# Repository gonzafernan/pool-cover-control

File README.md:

# Pool Cover Control Board

Electronic control board for an automatic residential pool cover. Drives a 24V DC brushed motor in both directions using a relay H-bridge, with inputs from a key switch and mechanical limit switches.

## Overview

The board replaces a failed original controller. It is designed for direct drop-in installation into the existing enclosure, preserving all external wiring and mechanical components.

## Hardware

- **MCU:** STM32G031K8T6 (ARM Cortex-M0+, 64MHz, no external crystal)
- **Motor control:** 4x SLA-24VDC-SL-C SPDT relays in H-bridge configuration, driven by ULN2003A
- **Power input:** 24V, 10A fused, from external 25A/600W PSU in the same enclosure
- **Logic supply:** 3.3V via LMR14206XMKE/NOPB synchronous buck converter
- **Inputs:** 3-position maintained key switch, two NC limit switches, isolated via PC817 optocouplers
- **Protection:** Reverse polarity (P-FET), motor TVS, relay hardware interlock, firmware watchdog
- **Manufacturer:** JLCPCB

## Firmware

- Toolchain: STM32CubeMX + Makefile + GCC
- State machine: IDLE / OPENING / CLOSING / FAULT
- Motor timeout: 60 seconds
- Internal IWDG watchdog enabled

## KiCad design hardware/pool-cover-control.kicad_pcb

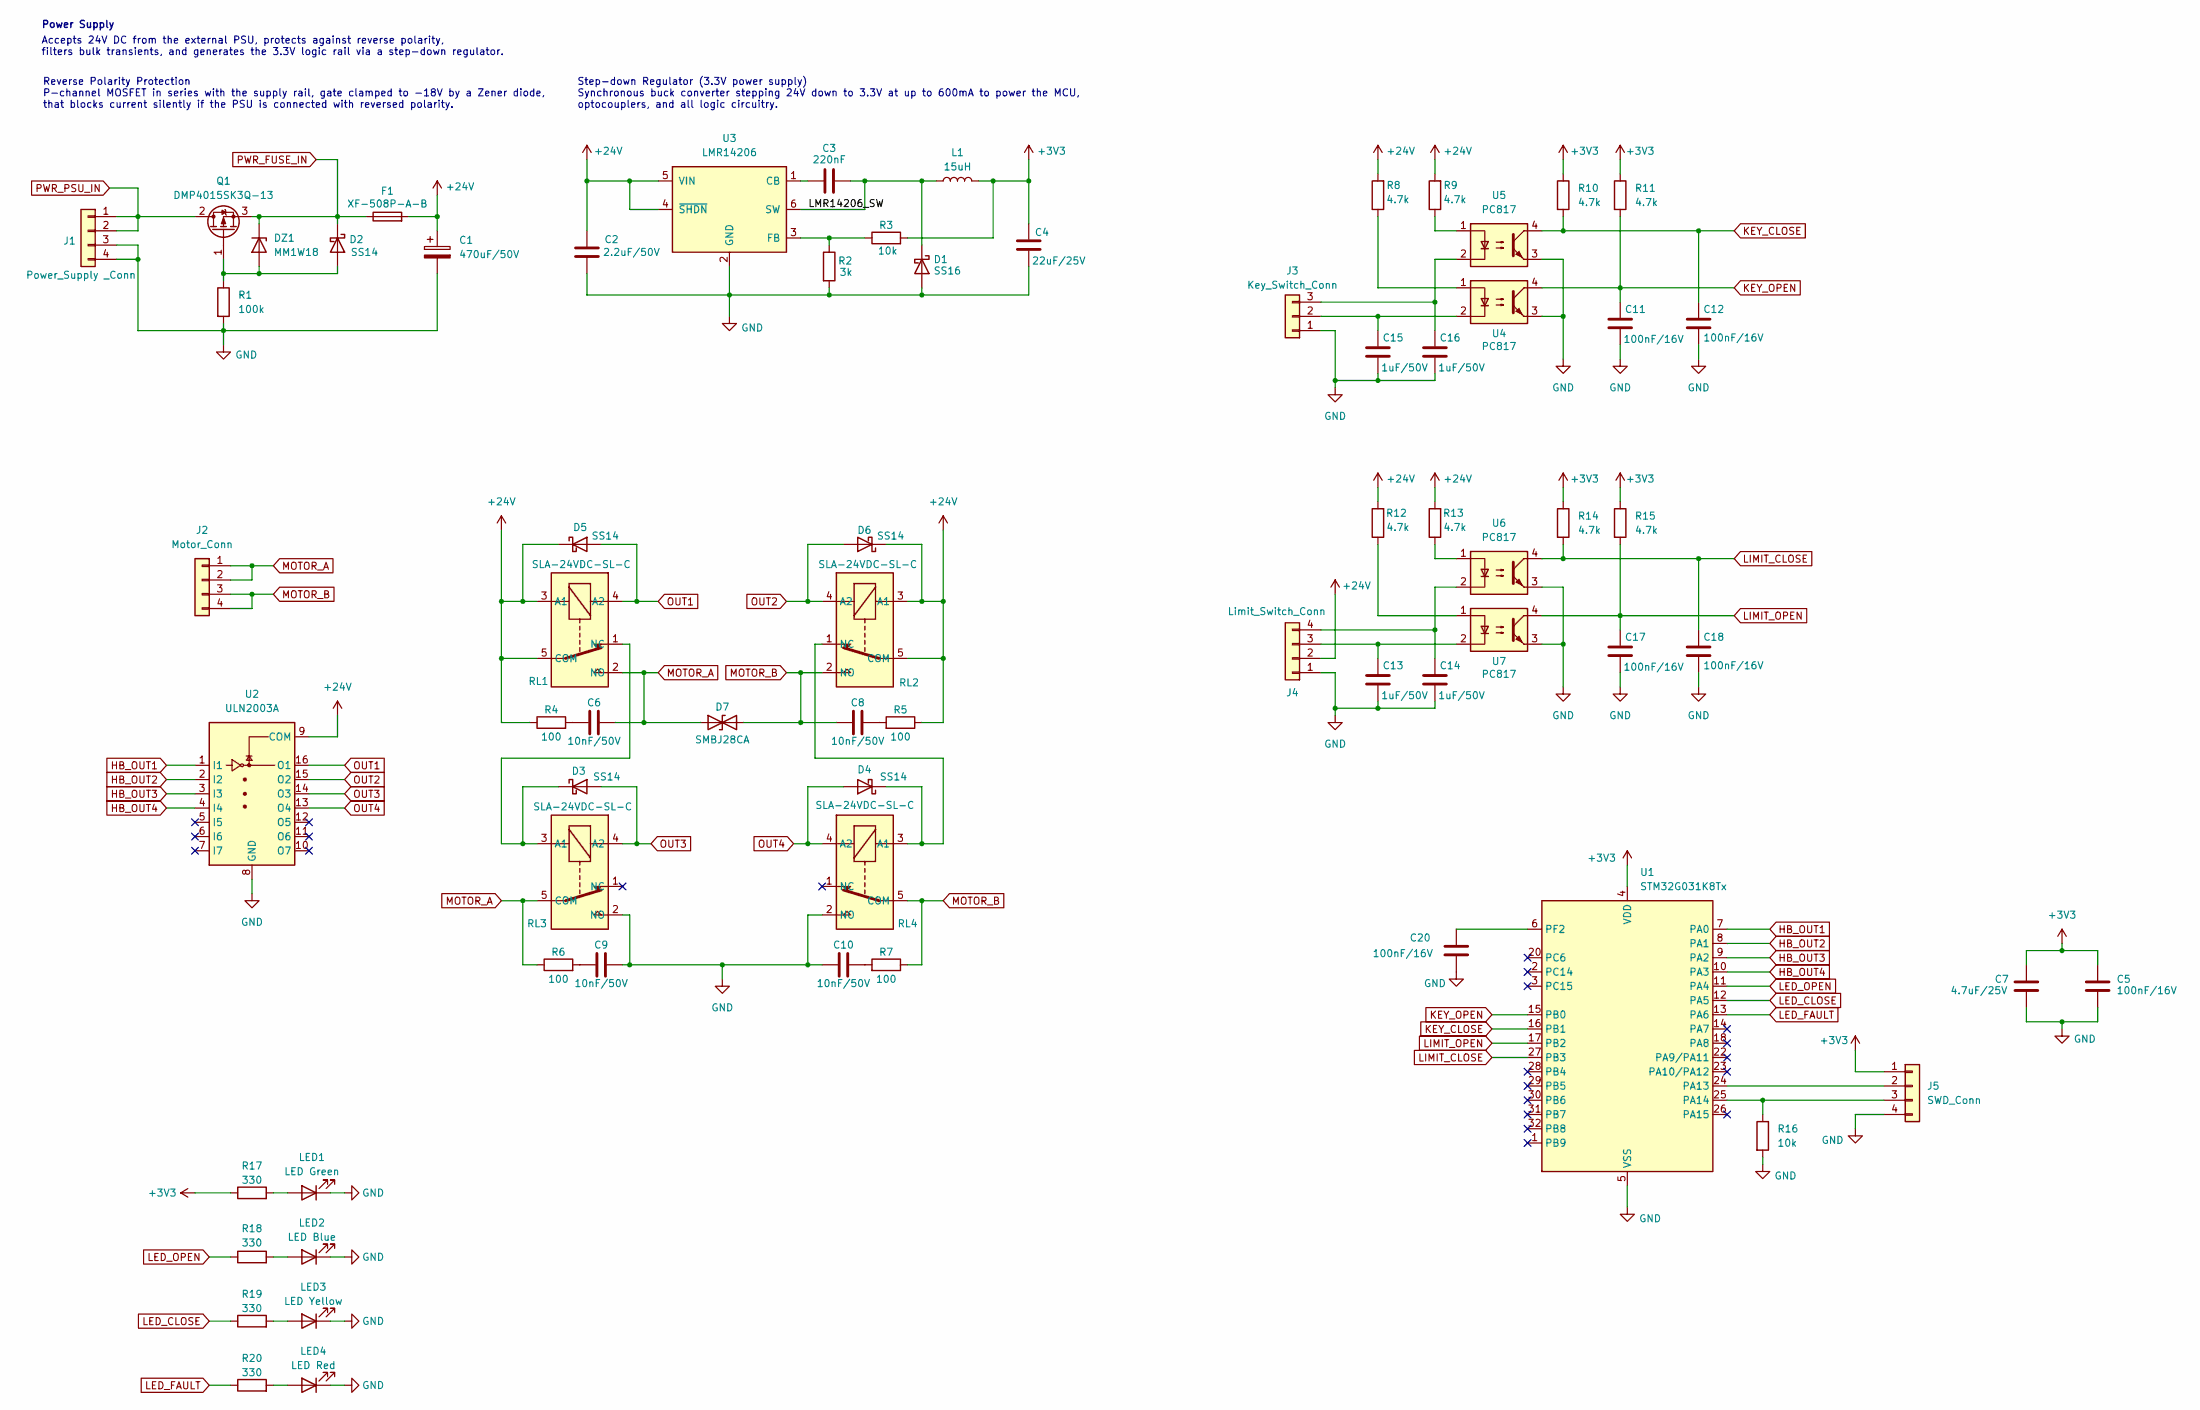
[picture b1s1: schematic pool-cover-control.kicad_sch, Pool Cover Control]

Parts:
C1: 470uF/50V; C_Radial_D10.0mm_H20.0mm_P5.00mm; LCSC C233099
C2: 2.2uF/50V; C_1206_3216Metric; LCSC 1206
C3: 220nF; C_0603_1608Metric; LCSC C21120
C4: 22uF/25V; C_1206_3216Metric; LCSC C12891
C5, C11, C12, C17, C18, C20: 100nF/16V; C_0402_1005Metric; LCSC C1525
C6, C8, C9, C10: 10nF/50V; C_0603_1608Metric; LCSC C57112
C7: 4.7uF/25V; C_0805_2012Metric; LCSC C1779
C13, C14, C15, C16: 1uF/50V; C_0603_1608Metric; LCSC C15849
D1: SS16; D_SMA; LCSC C908233
D2, D3, D4, D5, D6: SS14; D_SMA; LCSC C2480
D7: SMBJ28CA; D_SMB; LCSC C151259
DZ1: MM1W18; D_SOD-123; LCSC C382948
F1: XF-508P-A-B; Fuseholder_Blade_Mini_XFCN XF-508P-A-B; LCSC C19727304
J1: Power_Supply _Conn; TerminalBlock_Phoenix_MKDS-1,5-4-5.08_1x04_P5.08mm_Horizont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; LCSC C90087
J2: Motor_Conn; TerminalBlock_Phoenix_MKDS-1,5-4-5.08_1x04_P5.08mm_Horizont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; LCSC C90087
J3: Key_Switch_Conn; TerminalBlock_Phoenix_MKDS-1,5-3-5.08_1x03_P5.08mm_Horizont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; LCSC C91156
J4: Limit_Switch_Conn; TerminalBlock_Phoenix_MKDS-1,5-4-5.08_1x04_P5.08mm_Horizont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; LCSC C90087
J5: SWD_Conn; PinHeader_1x04_P2.54mm_Vertical; LCSC C2691448
L1: 15uH; L_Bourns_SRP7028A_7.3x6.6mm; LCSC C1847948
LED1: LED Green; LED_0603_1608Metric; LCSC C2286
LED2: LED Blue; LED_0603_1608Metric; LCSC C2286
LED3: LED Yellow; LED_0603_1608Metric; LCSC C2286
LED4: LED Red; LED_0603_1608Metric; LCSC C2286
Q1: DMP4015SK3Q-13; TO-252-3_TabPin2; LCSC C461089
R1: 100k; R_0402_1005Metric; LCSC C25741
R2: 3k; R_0603_1608Metric; LCSC C4211
R3, R16: 10k; R_0603_1608Metric; LCSC C25804
R4, R5, R6, R7: 100; R_0603_1608Metric; LCSC C22775
R8, R9, R12, R13: 4.7k; R_1206_3216Metric_Pad1.30x1.75mm_HandSolder; LCSC C17936
R10, R11, R14, R15: 4.7k; R_0402_1005Metric; LCSC C25900
R17, R18, R19, R20: 330; R_0402_1005Metric; LCSC C25104
RL1, RL2, RL3, RL4: SLA-24VDC-SL-C; SLA-XXVDC-SL-C; LCSC C187898
U1: STM32G031K8Tx; LQFP-32_7x7mm_P0.8mm; LCSC C724059
U2: ULN2003A; SOIC-16_3.9x9.9mm_P1.27mm; LCSC C7512
U3: LMR14206; SOT-23-6; LCSC C2071127
U4, U5, U6, U7: PC817; SOP-4_7.5x4.1mm_P2.54mm; LCSC C22447129

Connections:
+3V3: C4.2, C5.2, C7.2, J5.1, L1.2, R3.2, R10.1, R11.1, R14.1, R15.1, R17.1, U1.4 (VDD)
+24V: C1.1, C2.2, D5.1 (K), D6.1 (K), F1.2, J4.2, R4.1, R5.1, R8.2, R9.2, R12.2, R13.2, RL1.3 (A1), RL1.5 (COM), RL2.3 (A1), RL2.5 (COM), U2.9 (COM), U3.4 (~SHDN), U3.5 (VIN)
/LMR14206_SW: C3.2, D1.1 (K), L1.1, U3.6 (SW)
GND: C1.2, C2.1, C4.1, C5.1, C7.1, C9.2, C10.2, C11.1, C12.1, C13.1, C14.1, C15.1, C16.1, C17.1, C18.1, C20.1, D1.2 (A), J1.3, J1.4, J3.1, J4.1, J5.4, LED1.1 (K), LED2.1 (K), LED3.1 (K), LED4.1 (K), R1.2, R2.2, R16.2, RL3.2 (NO), RL4.2 (NO), U1.5 (VSS), U2.8 (GND), U3.2 (GND), U4.3, U5.3, U6.3, U7.3
HB_OUT1: U1.7 (PA0), U2.1 (I1)
HB_OUT2: U1.8 (PA1), U2.2 (I2)
HB_OUT3: U1.9 (PA2), U2.3 (I3)
HB_OUT4: U1.10 (PA3), U2.4 (I4)
KEY_CLOSE: C12.2, R10.2, U1.16 (PB1), U5.4
KEY_OPEN: C11.2, R11.2, U1.15 (PB0), U4.4
LED_CLOSE: R19.1, U1.12 (PA5)
LED_FAULT: R20.1, U1.13 (PA6)
LED_OPEN: R18.1, U1.11 (PA4)
LIMIT_CLOSE: C18.2, R14.2, U1.27 (PB3), U6.4
LIMIT_OPEN: C17.2, R15.2, U1.17 (PB2), U7.4
MOTOR_A: C6.2, D7.1 (A1), J2.1, J2.2, R6.1, RL1.2 (NO), RL3.5 (COM)
MOTOR_B: C8.2, D7.2 (A2), J2.3, J2.4, R7.1, RL2.2 (NO), RL4.5 (COM)
unnamed: C6.1, R4.2
unnamed: C8.1, R5.2
unnamed: C9.1, R6.2
unnamed: C10.1, R7.2
unnamed: D2.2 (A), DZ1.2 (A), Q1.1 (G), R1.1
unnamed: D3.1 (K), RL1.1 (NC), RL3.3 (A1)
unnamed: D4.1 (K), RL2.1 (NC), RL4.3 (A1)
unnamed: C15.2, J3.2, U4.2
unnamed: C16.2, J3.3, U5.2
unnamed: C13.2, J4.3, U7.2
unnamed: C14.2, J4.4, U6.2
unnamed: J5.2, U1.24 (PA13)
unnamed: J5.3, R16.1, U1.25 (PA14)
unnamed: LED1.2 (A), R17.2
unnamed: LED2.2 (A), R18.2
unnamed: LED3.2 (A), R19.2
unnamed: LED4.2 (A), R20.2
unnamed: R8.1, U4.1
unnamed: R9.1, U5.1
unnamed: R12.1, U7.1
unnamed: R13.1, U6.1
unnamed: C20.2, U1.6 (PF2)
unnamed: C3.1, U3.1 (CB)
unnamed: R2.1, R3.1, U3.3 (FB)
OUT1: D5.2 (A), RL1.4 (A2), U2.16 (O1)
OUT2: D6.2 (A), RL2.4 (A2), U2.15 (O2)
OUT3: D3.2 (A), RL3.4 (A2), U2.14 (O3)
OUT4: D4.2 (A), RL4.4 (A2), U2.13 (O4)
PWR_FUSE_IN: D2.1 (K), DZ1.1 (K), F1.1, Q1.3 (S)
PWR_PSU_IN: J1.1, J1.2, Q1.2 (D)

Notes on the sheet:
Reverse Polarity Protection P-channel MOSFET in series with the supply rail, gate clamped to −18V by a Zener diode, that blocks current silently if the PSU is connected with reversed polarity.
Power Supply
Accepts 24V DC from the external PSU, protects against reverse polarity, filters bulk transients, and generates the 3.3V logic rail via a step-down regulator.
Step-down Regulator (3.3V power supply) Synchronous buck converter stepping 24V down to 3.3V at up to 600mA to power the MCU, optocouplers, and all logic circuitry.

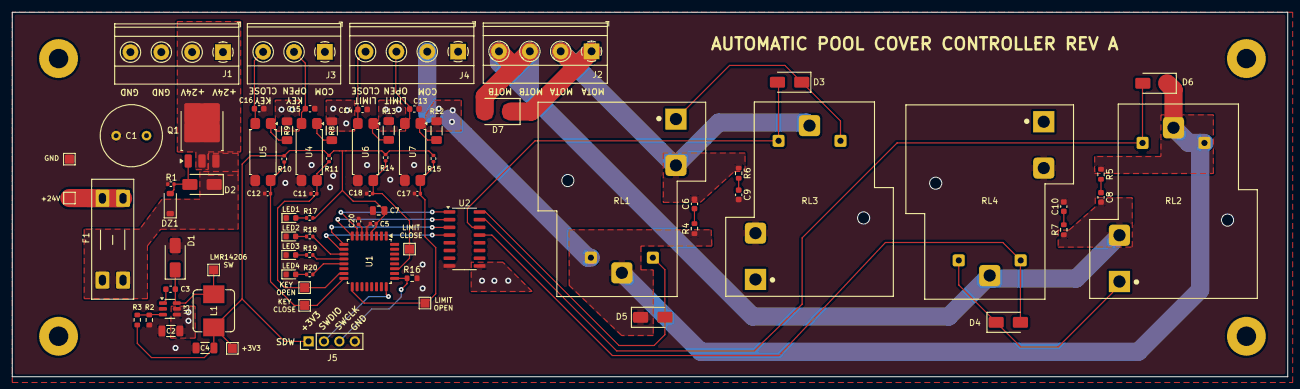
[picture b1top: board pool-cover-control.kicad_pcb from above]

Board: 2 copper layers, 210.0 x 60.0 mm, 70 parts (0 on the bottom side), 47 nets.

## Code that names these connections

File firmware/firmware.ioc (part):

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Mcu.Name=STM32G031K(4-6-8)Tx
Mcu.Package=LQFP32
Mcu.UserName=STM32G031K8Tx
PA0.GPIOParameters=GPIO_Label
PA0.GPIO_Label=HB_OUT1
PA0.Signal=GPIO_Output
PA1.GPIOParameters=GPIO_Label
PA1.GPIO_Label=HB_OUT2
PA1.Signal=GPIO_Output
PA13.Mode=Serial_Wire
PA13.Signal=SYS_SWDIO
PA14-BOOT0.Mode=Serial_Wire
PA14-BOOT0.Signal=SYS_SWCLK
PA2.GPIOParameters=GPIO_Label
PA2.GPIO_Label=HB_OUT3
PA2.Signal=GPIO_Output
PA3.GPIOParameters=GPIO_Label
PA3.GPIO_Label=HB_OUT4
PA3.Signal=GPIO_Output
PA4.GPIOParameters=GPIO_Label
PA4.GPIO_Label=LED_OPEN
PA4.Signal=GPIO_Output
PA5.GPIOParameters=GPIO_Label
PA5.GPIO_Label=LED_CLOSE
PA5.Signal=GPIO_Output
PA6.GPIOParameters=GPIO_Label
PA6.GPIO_Label=LED_FAULT
PA6.Signal=GPIO_Output
PB0.GPIOParameters=GPIO_Label
PB0.GPIO_Label=KEY_OPEN
PB0.Signal=GPIO_Input
PB1.GPIOParameters=GPIO_Label
PB1.GPIO_Label=KEY_CLOSE
PB1.Signal=GPIO_Input
RCC.HSE_VALUE=8000000
RCC.SYSCLKFreq_VALUE=16000000
board=custom

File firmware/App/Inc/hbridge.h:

/**
 * @file hbridge.h
 * @author Gonzalo G. Fernandez
 *
 */

#ifndef HBRIDGE_H_
#define HBRIDGE_H_

#ifdef __cplusplus
extern "C" {
#endif

#include <stdint.h>

#include "stm32g0xx_hal.h"

typedef enum {
  HBRIDGE_NONE = 0,
  HBRIDGE_POSITIVE,
  HBRIDGE_NEGATIVE,
} hbridge_state_t;

void hbridge_init(GPIO_TypeDef *out1_port, uint16_t out1_pin,
                  GPIO_TypeDef *out2_port, uint16_t out2_pin,
                  GPIO_TypeDef *out3_port, uint16_t out3_pin,
                  GPIO_TypeDef *out4_port, uint16_t out4_pin);

void hbridge_set_state(hbridge_state_t state);

#ifdef __cplusplus
}
#endif

#endif /* HBRIDGE_H_ */

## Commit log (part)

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2026-05-26 docs: add project documentation, design spec, roadmap and preferences
2026-05-26 chore(hardware): add BOM with confirmed LCSC part numbers
2026-05-26 chore(project): init KiCad project and add gitignore
2026-05-27 fix(hardware): replace relay with SLA-12VDC-SL-C and correct BOM entries
2026-06-17 feat(hardware): add custom SLA-12VDC-SL-C symbol and footprint
